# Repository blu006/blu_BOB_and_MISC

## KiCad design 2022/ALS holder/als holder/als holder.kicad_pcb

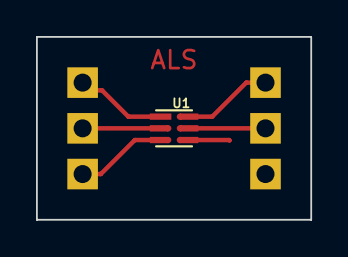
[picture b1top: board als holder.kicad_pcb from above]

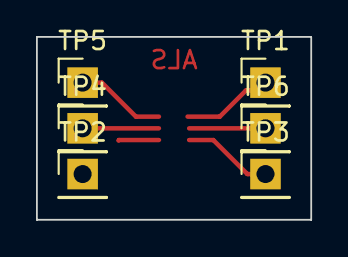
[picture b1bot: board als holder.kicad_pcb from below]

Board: 2 copper layers, 15.2 x 10.2 mm, 7 parts (6 on the bottom side), 5 nets.

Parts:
TP1, TP2, TP3, TP4, TP5, TP6: TestPoint_Small; PinHeader_1x01_P2.54mm_Vertical
U1: TSL2572; AMS_TSL2572_SMD

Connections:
GND: TP3.1, U1.3 (GND)
unnamed: TP4.1, U1.5 (INT)
unnamed: TP5.1, U1.6 (SDA)
unnamed: TP6.1, U1.2 (SCL)
VDD: TP1.1, U1.1 (VDD)

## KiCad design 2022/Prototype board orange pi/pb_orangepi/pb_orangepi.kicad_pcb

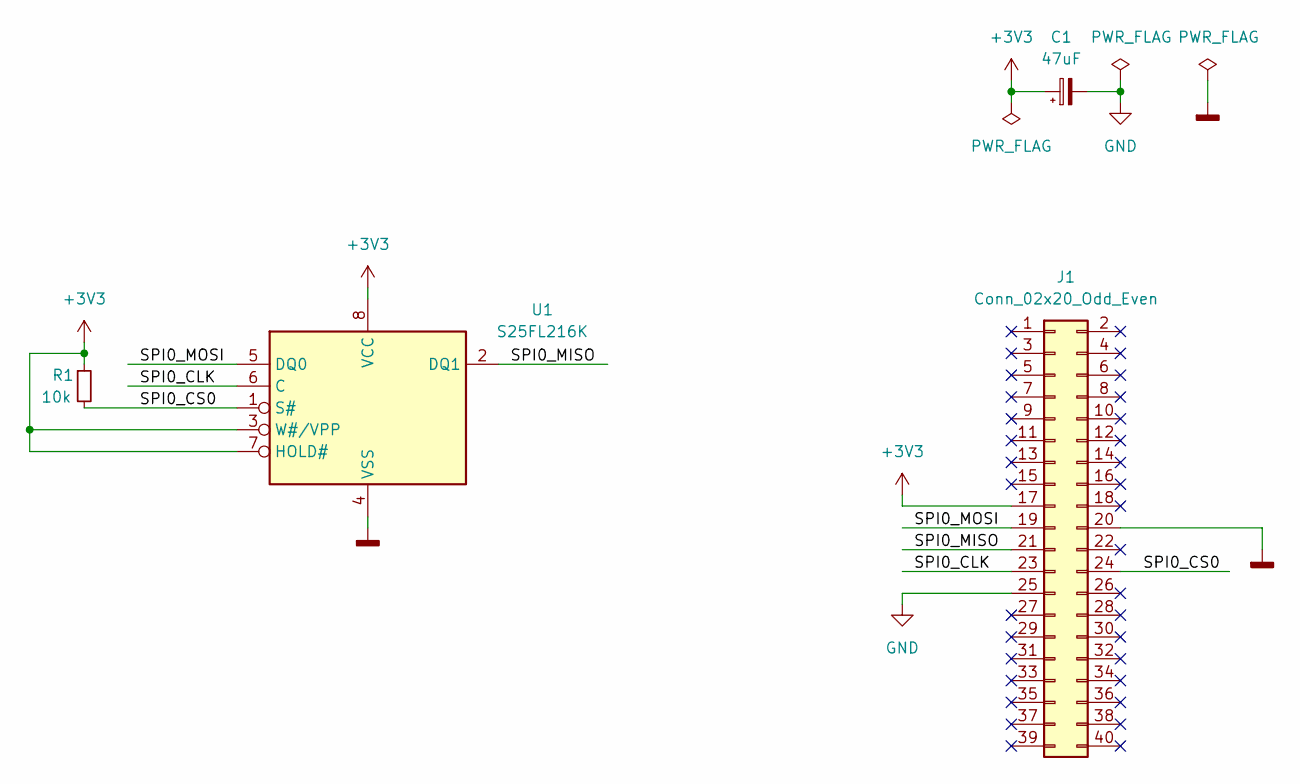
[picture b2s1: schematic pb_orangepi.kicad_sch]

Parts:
C1: 47uF; CP_Radial_D7.5mm_P2.50mm
J1: Conn_02x20_Odd_Even; PinSocket_2x20_P2.54mm_Vertical
R1: 10k; R_0805_2012Metric
U1: S25FL216K; SOIC-8W_5.3x5.3mm_P1.27mm

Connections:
+3V3: C1.1, J1.17, R1.1, U1.3 (W#/VPP), U1.7 (HOLD#), U1.8 (VCC)
/SPI0_CLK: J1.23, U1.6 (C)
/SPI0_CS0: J1.24, R1.2, U1.1 (S#)
/SPI0_MISO: J1.21, U1.2 (DQ1)
/SPI0_MOSI: J1.19, U1.5 (DQ0)
GND: C1.2, J1.25
GNDD: J1.20, U1.4 (VSS)

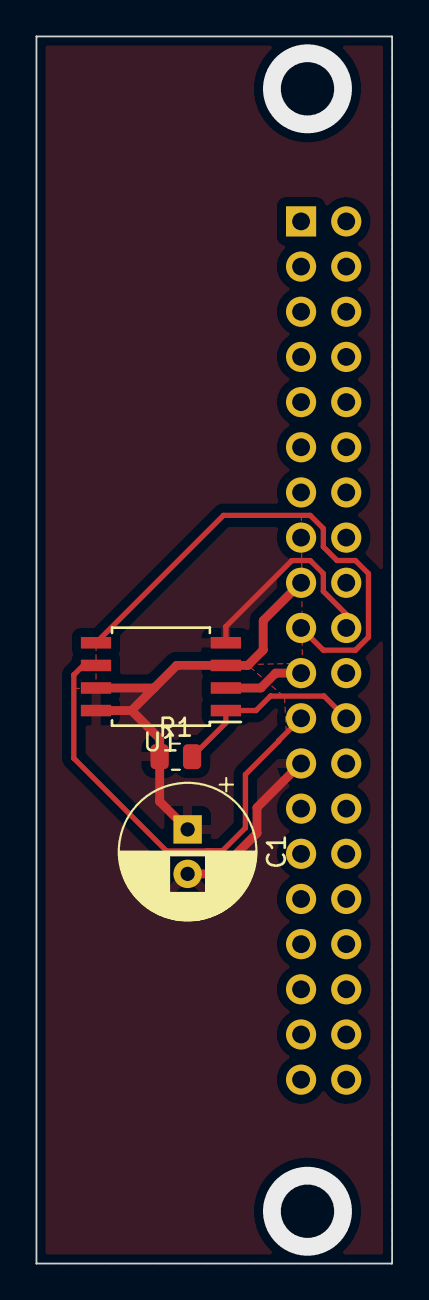
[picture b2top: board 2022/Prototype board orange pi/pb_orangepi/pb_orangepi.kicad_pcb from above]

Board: 2 copper layers, 20.0 x 69.0 mm, 4 parts (1 on the bottom side), 7 nets.

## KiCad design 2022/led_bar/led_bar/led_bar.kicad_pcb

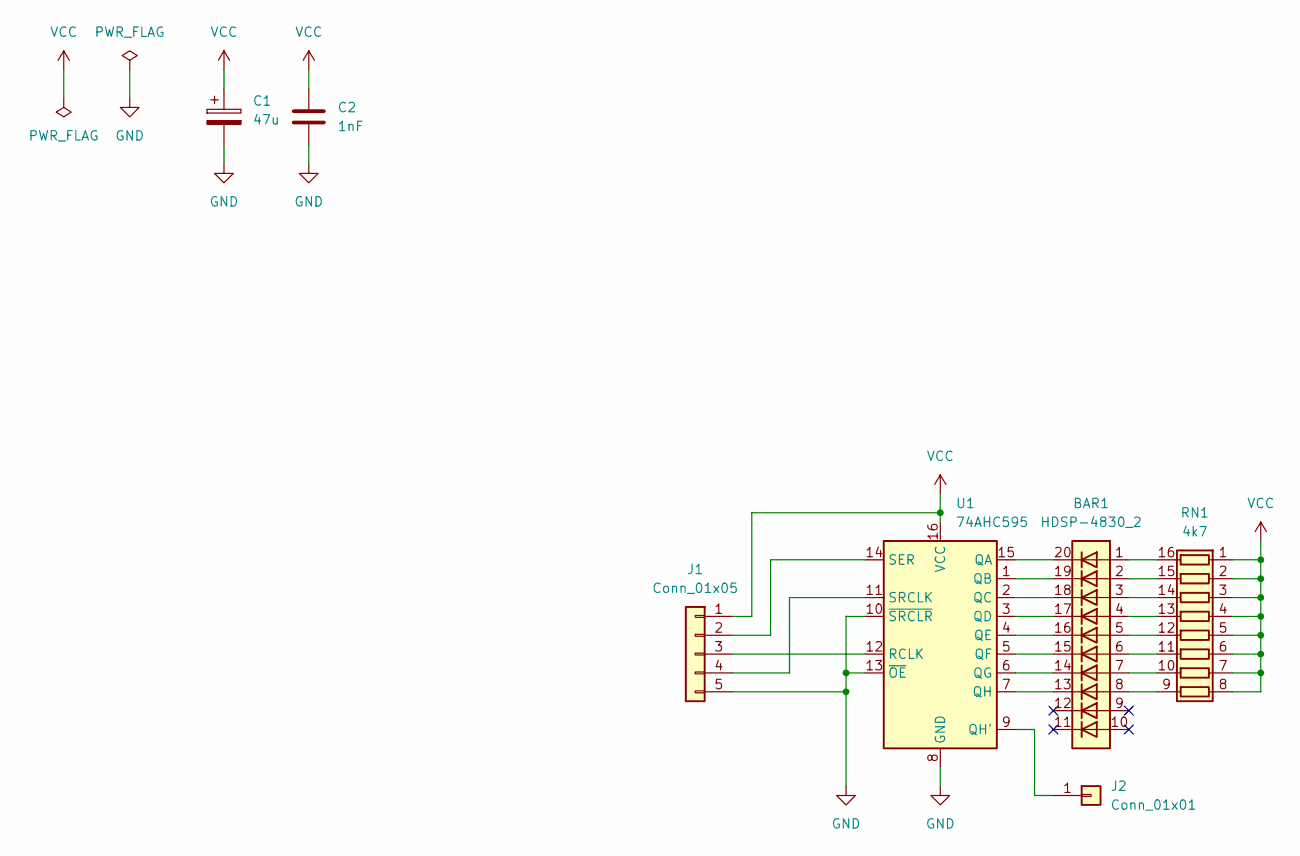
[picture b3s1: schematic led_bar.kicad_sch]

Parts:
BAR1: HDSP-4830_2; HDSP-4830
C1: 47u; CP_Radial_D8.0mm_P3.50mm
C2: 1nF; C_0805_2012Metric
J1: Conn_01x05; PinSocket_1x05_P2.54mm_Vertical
J2: Conn_01x01
RN1: 4k7; DIP-16_W7.62mm
U1: 74AHC595; DIP-16_W7.62mm

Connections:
GND: C1.2, C2.2, J1.5, U1.8 (GND), U1.10 (~SRCLR), U1.13 (~OE)
unnamed: BAR1.1 (A), RN1.16 (R1.2)
unnamed: BAR1.2 (A), RN1.15 (R2.2)
unnamed: BAR1.3 (A), RN1.14 (R3.2)
unnamed: BAR1.4 (A), RN1.13 (R4.2)
unnamed: BAR1.5 (A), RN1.12 (R5.2)
unnamed: BAR1.6 (A), RN1.11 (R6.2)
unnamed: BAR1.7 (A), RN1.10 (R7.2)
unnamed: BAR1.8 (A), RN1.9 (R8.2)
unnamed: BAR1.13 (K), U1.7 (QH)
unnamed: BAR1.14 (K), U1.6 (QG)
unnamed: BAR1.15 (K), U1.5 (QF)
unnamed: BAR1.16 (K), U1.4 (QE)
unnamed: BAR1.17 (K), U1.3 (QD)
unnamed: BAR1.18 (K), U1.2 (QC)
unnamed: BAR1.19 (K), U1.1 (QB)
unnamed: BAR1.20 (K), U1.15 (QA)
unnamed: J1.2, U1.14 (SER)
unnamed: J1.3, U1.12 (RCLK)
unnamed: J1.4, U1.11 (SRCLK)
unnamed: J2.1, U1.9 (QH')
VCC: C1.1, C2.1, J1.1, RN1.1 (R1.1), RN1.2 (R2.1), RN1.3 (R3.1), RN1.4 (R4.1), RN1.5 (R5.1), RN1.6 (R6.1), RN1.7 (R7.1), RN1.8 (R8.1), U1.16 (VCC)

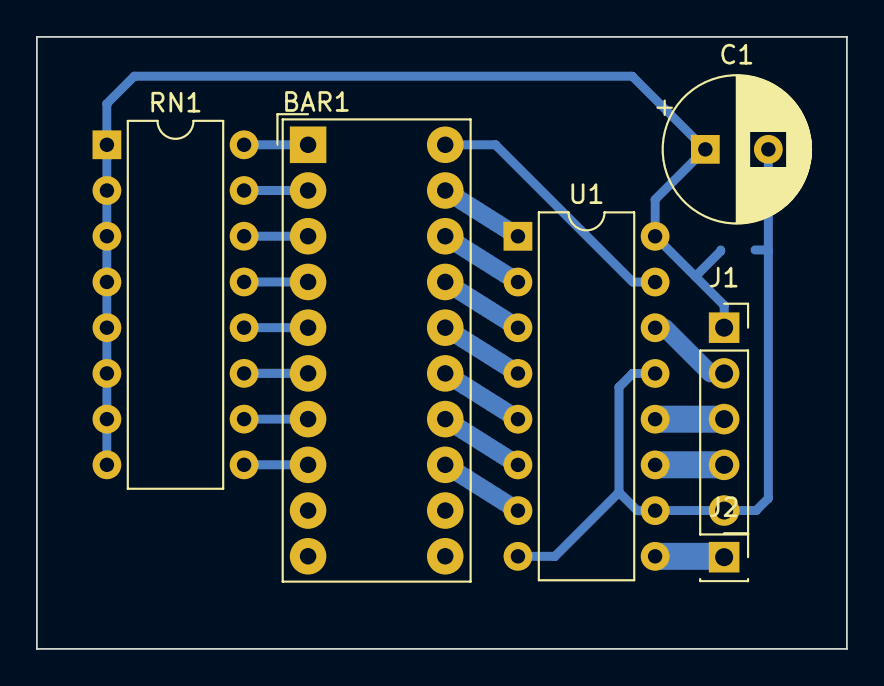
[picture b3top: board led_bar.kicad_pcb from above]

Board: 2 copper layers, 45.0 x 34.0 mm, 7 parts (1 on the bottom side), 22 nets.

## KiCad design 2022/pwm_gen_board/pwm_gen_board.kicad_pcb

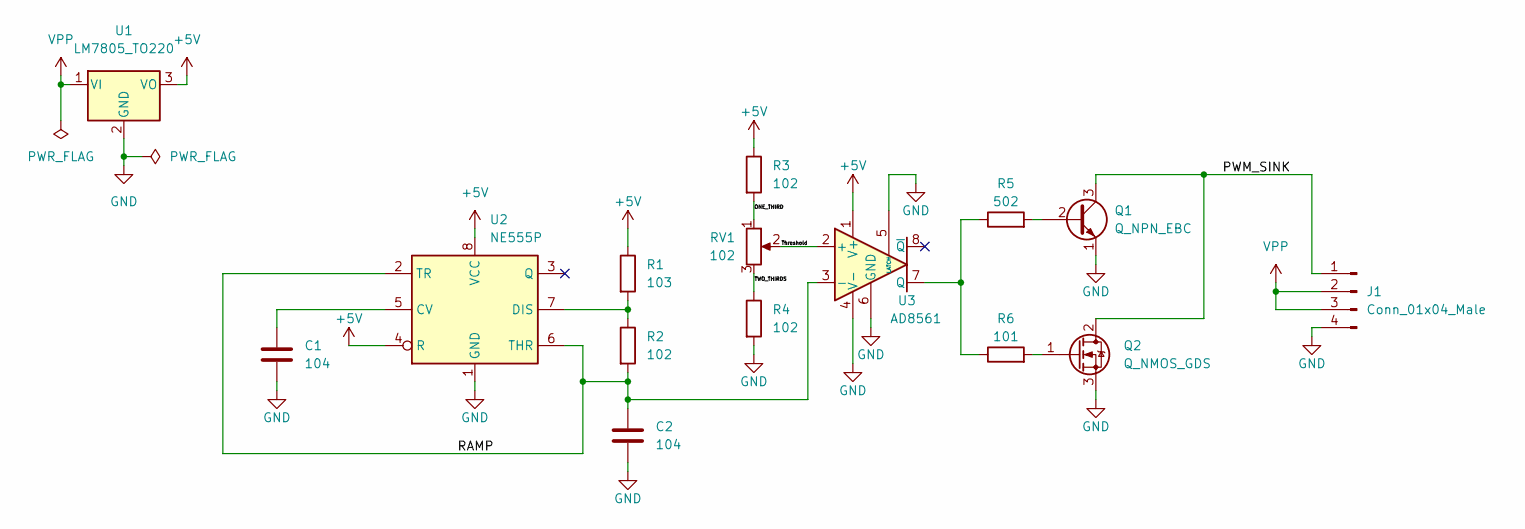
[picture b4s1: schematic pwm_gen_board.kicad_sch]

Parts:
C1, C2: 104; C_0805_2012Metric
J1: Conn_01x04_Male; TerminalBlock_bornier-4_P5.08mm
Q1: Q_NPN_EBC; TO-92
Q2: Q_NMOS_GDS; TO-220-3_Vertical
R1: 103; R_0805_2012Metric
R2, R3, R4: 102; R_0805_2012Metric
R5: 502; R_0805_2012Metric
R6: 101; R_0805_2012Metric
RV1: 102; JST_XH_B3B-XH-AM_1x03_P2.50mm_Vertical
U1: LM7805_TO220; TO-220-3_Vertical
U2: NE555P; DIP-8_W7.62mm
U3: AD8561; DIP-8_W7.62mm

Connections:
+5V: R1.1, R3.1, U1.3 (VO), U2.4 (R), U2.8 (VCC), U3.1 (V+)
/ONE_THIRD: R3.2, RV1.1
/PWM_SINK: J1.1, Q1.3 (C), Q2.2 (D)
/RAMP: C2.1, R2.2, U2.2 (TR), U2.6 (THR), U3.3 (-)
/TWO_THIRDS: R4.1, RV1.3
/Threshold: RV1.2, U3.2 (+)
GND: C1.2, C2.2, J1.4, Q1.1 (E), Q2.3 (S), R4.2, U1.2 (GND), U2.1 (GND), U3.4 (V-), U3.5 (LATCH), U3.6 (GND)
unnamed: C1.1, U2.5 (CV)
unnamed: Q1.2 (B), R5.2
unnamed: Q2.1 (G), R6.2
unnamed: R1.2, R2.1, U2.7 (DIS)
unnamed: R5.1, R6.1, U3.7 (Q)
VPP: J1.2, J1.3, U1.1 (VI)

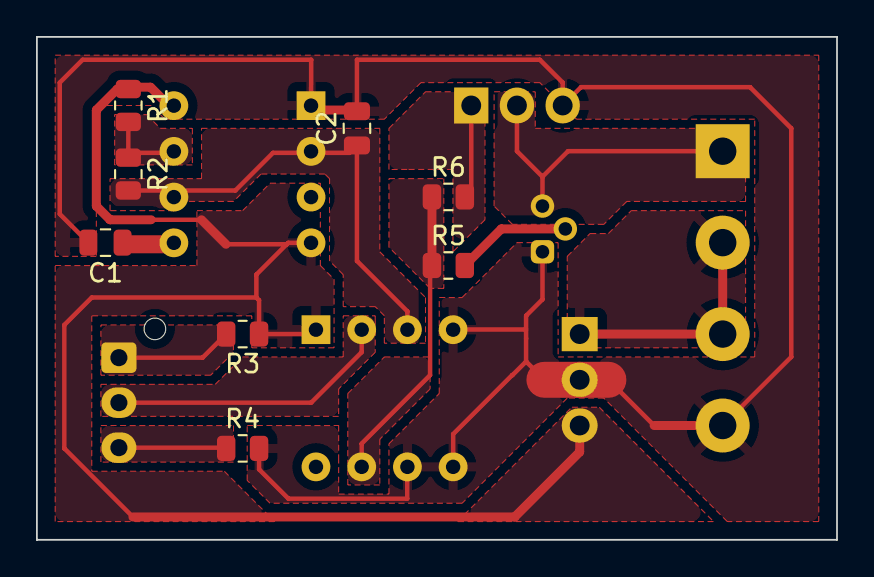
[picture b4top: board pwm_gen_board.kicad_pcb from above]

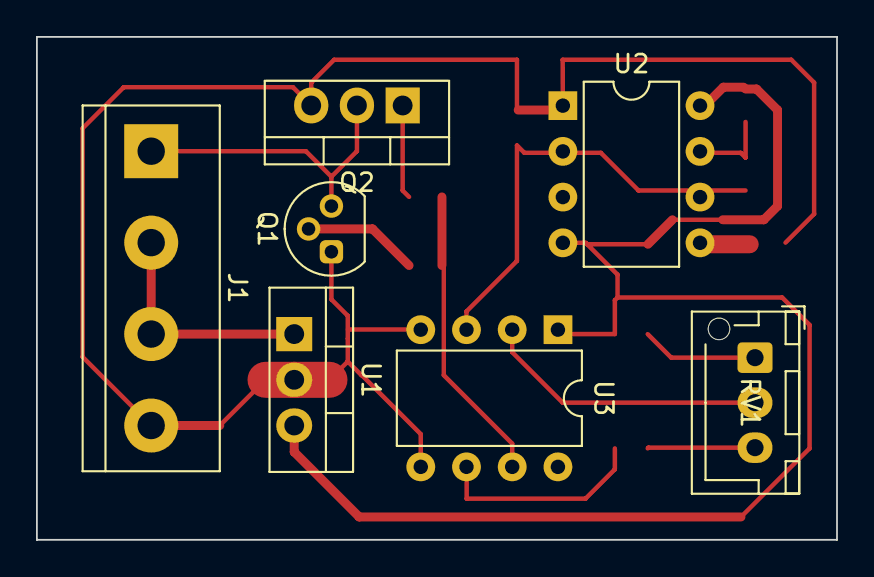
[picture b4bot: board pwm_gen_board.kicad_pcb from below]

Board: 2 copper layers, 44.5 x 27.9 mm, 15 parts (7 on the bottom side), 13 nets.

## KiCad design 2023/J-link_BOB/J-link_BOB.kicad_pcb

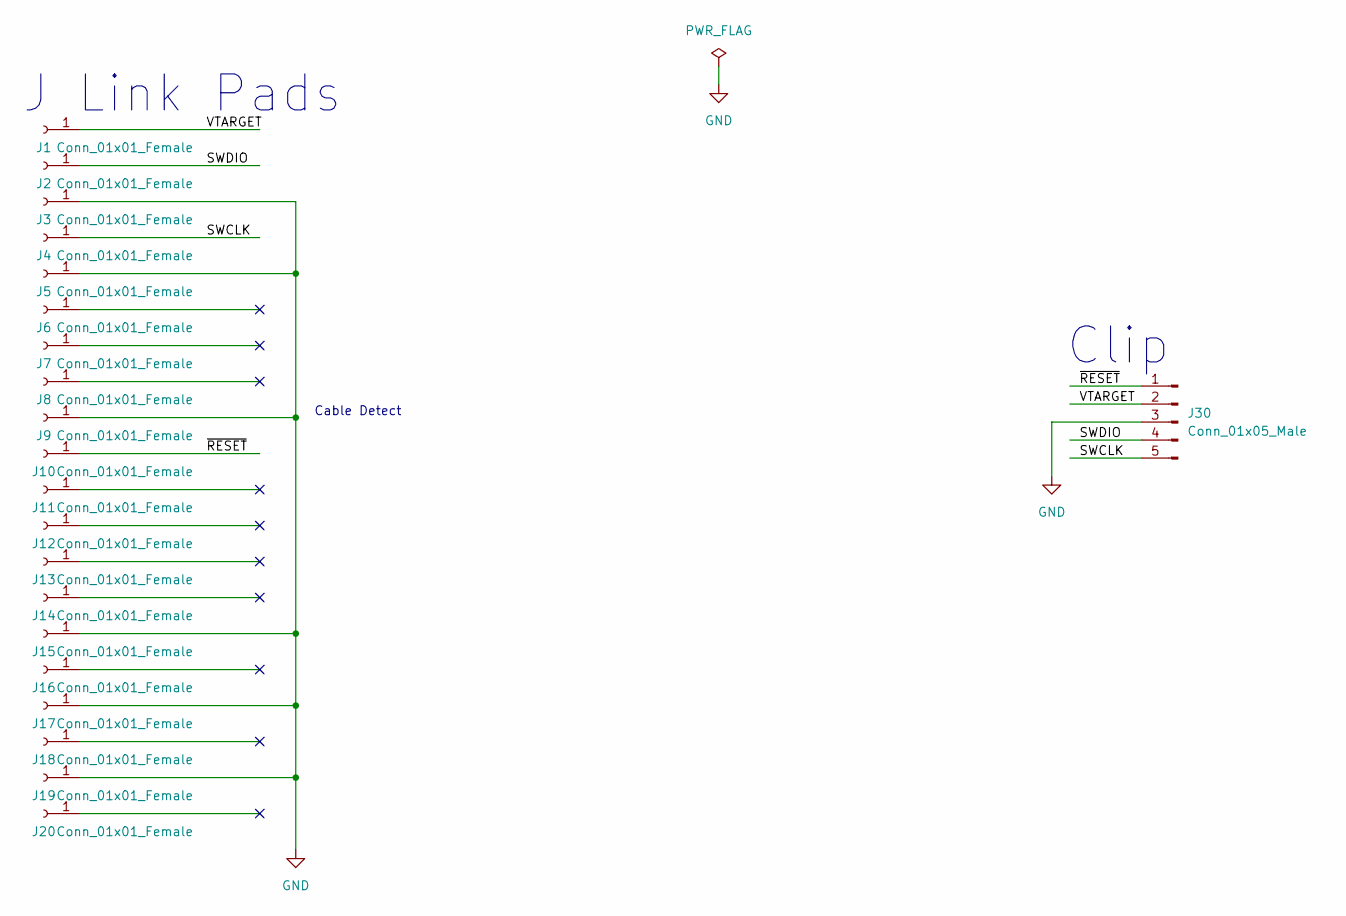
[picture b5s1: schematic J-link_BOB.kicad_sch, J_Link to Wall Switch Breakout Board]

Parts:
J1, J2, J3, J4, J5, J6, J7, J8, J9, J10, J11, J12, J13, J14, J15, J16, J17, J18, J19, J20: Conn_01x01_Female; PAD_2.5x0.65mm
J30: Conn_01x05_Male; PinHeader_1x05_P2.54mm_Horizontal

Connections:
/SWCLK: J4.1, J30.5
/SWDIO: J2.1, J30.4
/VTARGET: J1.1, J30.2
/~RESET: J10.1, J30.1
GND: J3.1, J5.1, J9.1, J15.1, J17.1, J19.1, J30.3

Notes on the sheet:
Clip
J Link Pads
Cable Detect

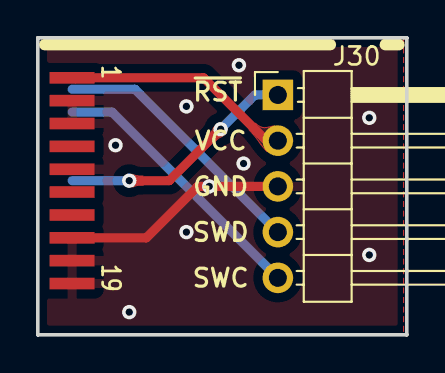
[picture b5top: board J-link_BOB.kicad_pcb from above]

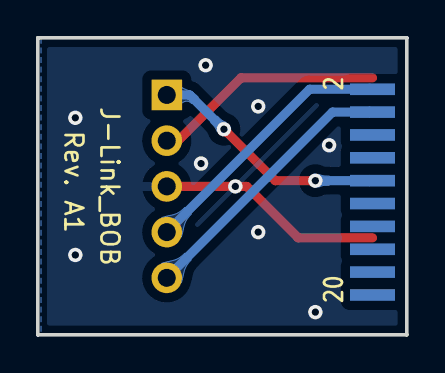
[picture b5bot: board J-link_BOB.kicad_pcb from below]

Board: 2 copper layers, 20.5 x 16.5 mm, 21 parts (10 on the bottom side), 5 nets.

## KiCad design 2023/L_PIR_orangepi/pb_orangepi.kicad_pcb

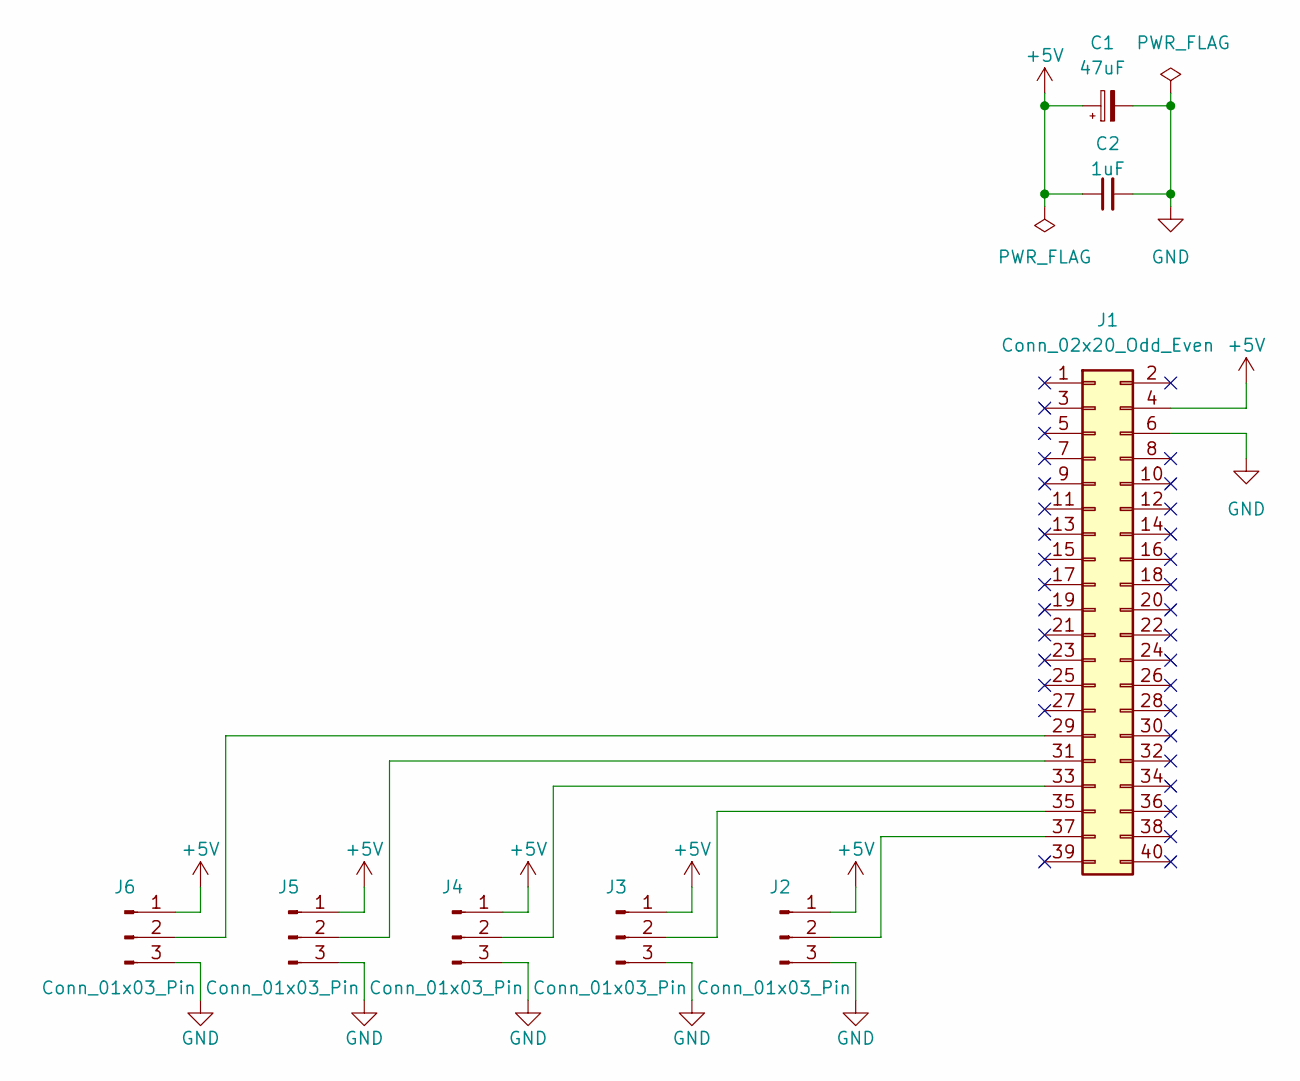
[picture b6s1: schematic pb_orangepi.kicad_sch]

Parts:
C1: 47uF; CP_Radial_D7.5mm_P2.50mm
C2: 1uF; C_0805_2012Metric
J1: Conn_02x20_Odd_Even; PinSocket_2x20_P2.54mm_Vertical
J2, J3, J4, J5, J6: Conn_01x03_Pin; PinHeader_1x03_P2.54mm_Horizontal_SMD_BoardEdge_Right

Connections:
+5V: C1.1, C2.1, J1.4, J2.1, J3.1, J4.1, J5.1, J6.1
GND: C1.2, C2.2, J1.6, J2.3, J3.3, J4.3, J5.3, J6.3
unnamed: J1.29, J6.2
unnamed: J1.31, J5.2
unnamed: J1.33, J4.2
unnamed: J1.35, J3.2
unnamed: J1.37, J2.2

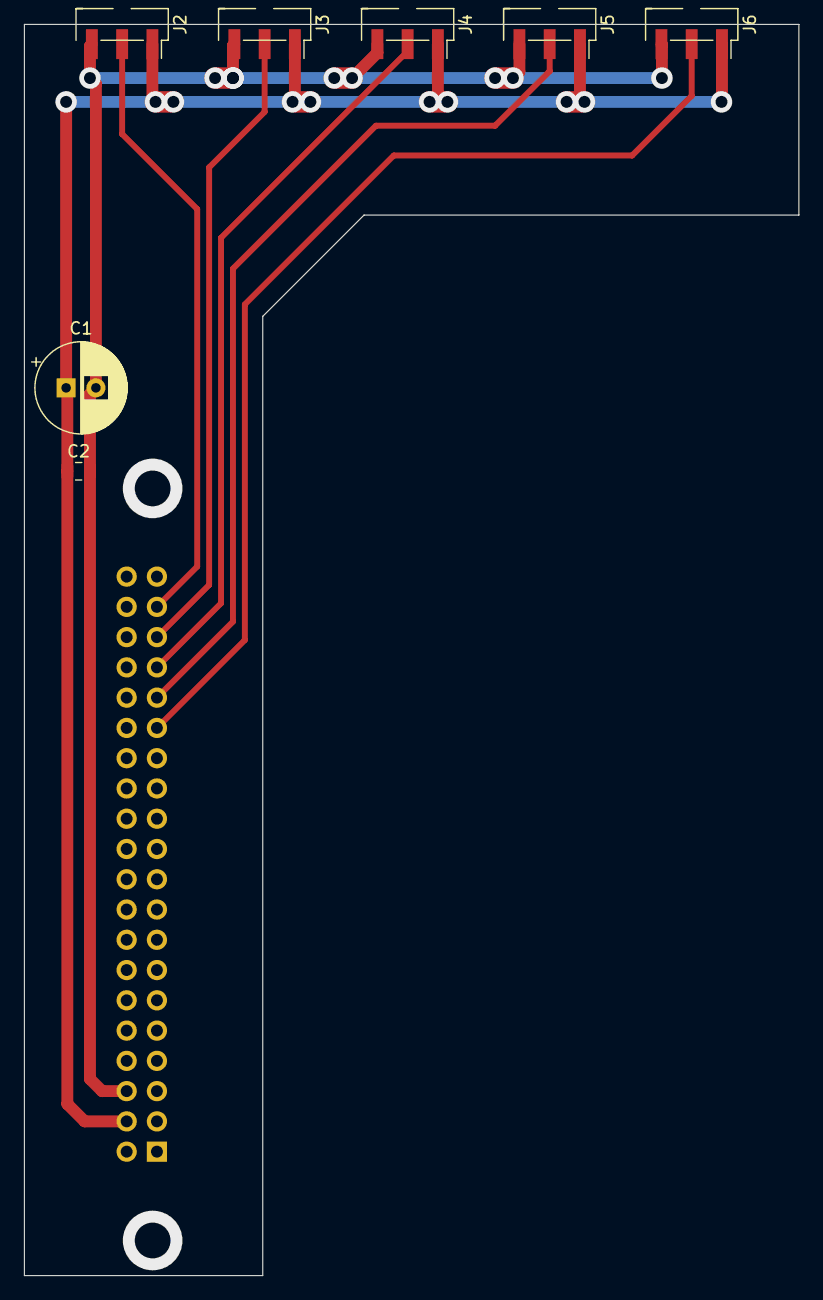
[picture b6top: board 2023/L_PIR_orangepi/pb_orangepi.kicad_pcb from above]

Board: 2 copper layers, 65.0 x 105.0 mm, 8 parts (1 on the bottom side), 7 nets.

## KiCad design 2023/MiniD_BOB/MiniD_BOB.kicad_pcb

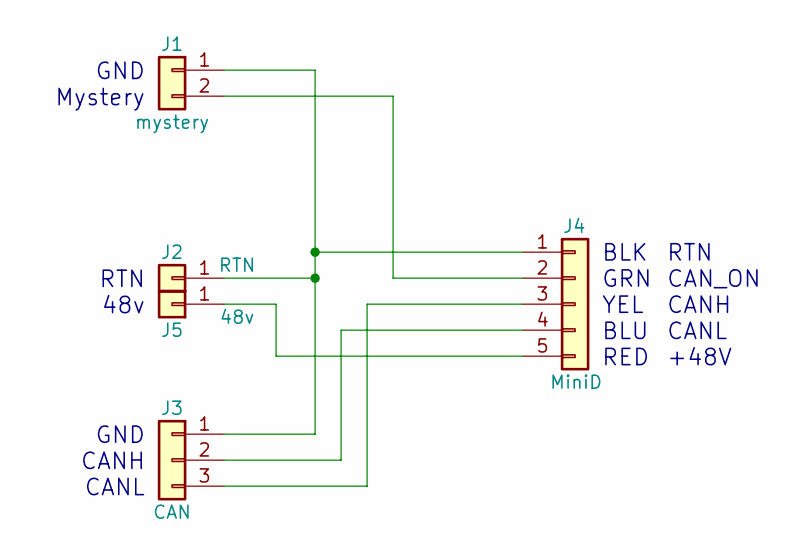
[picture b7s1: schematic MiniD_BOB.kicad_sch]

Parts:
J1: mystery; PinSocket_1x02_P2.54mm_Vertical
J2: RTN; SolderWirePad_1x01_SMD_1x2mm
J3: CAN; PinSocket_1x03_P2.54mm_Vertical
J4: MiniD; JST_PH_B5B-PH-SM4-TB_1x05-1MP_P2.00mm_Vertical
J5: 48v; SolderWirePad_1x01_SMD_1x2mm

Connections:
unnamed: J1.1, J2.1, J3.1, J4.1
unnamed: J1.2, J4.2
unnamed: J3.2, J4.4
unnamed: J3.3, J4.3
unnamed: J4.5, J5.1

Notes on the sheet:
RTN 48v
BLK GRN YEL BLU RED
GND CANH CANL
GND Mystery
RTN CAN_ON CANH CANL +48V

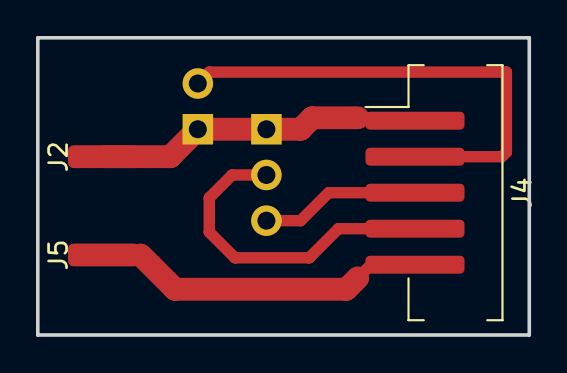
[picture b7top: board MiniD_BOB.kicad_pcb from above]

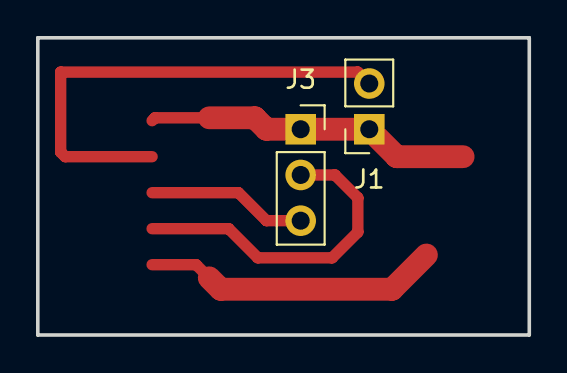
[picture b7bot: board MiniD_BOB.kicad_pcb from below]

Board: 2 copper layers, 27.3 x 16.5 mm, 5 parts (2 on the bottom side), 5 nets.
